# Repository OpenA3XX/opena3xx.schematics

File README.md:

# OpenA3XX Schematics & PCBs

## OpenA3XX Digital Hardare Controller Board (HCB)

## OpenA3XX MCDU with embedded HCB (Optional)
### Front View

### Back View

## OpenA3XX IO Terminal Block Boards

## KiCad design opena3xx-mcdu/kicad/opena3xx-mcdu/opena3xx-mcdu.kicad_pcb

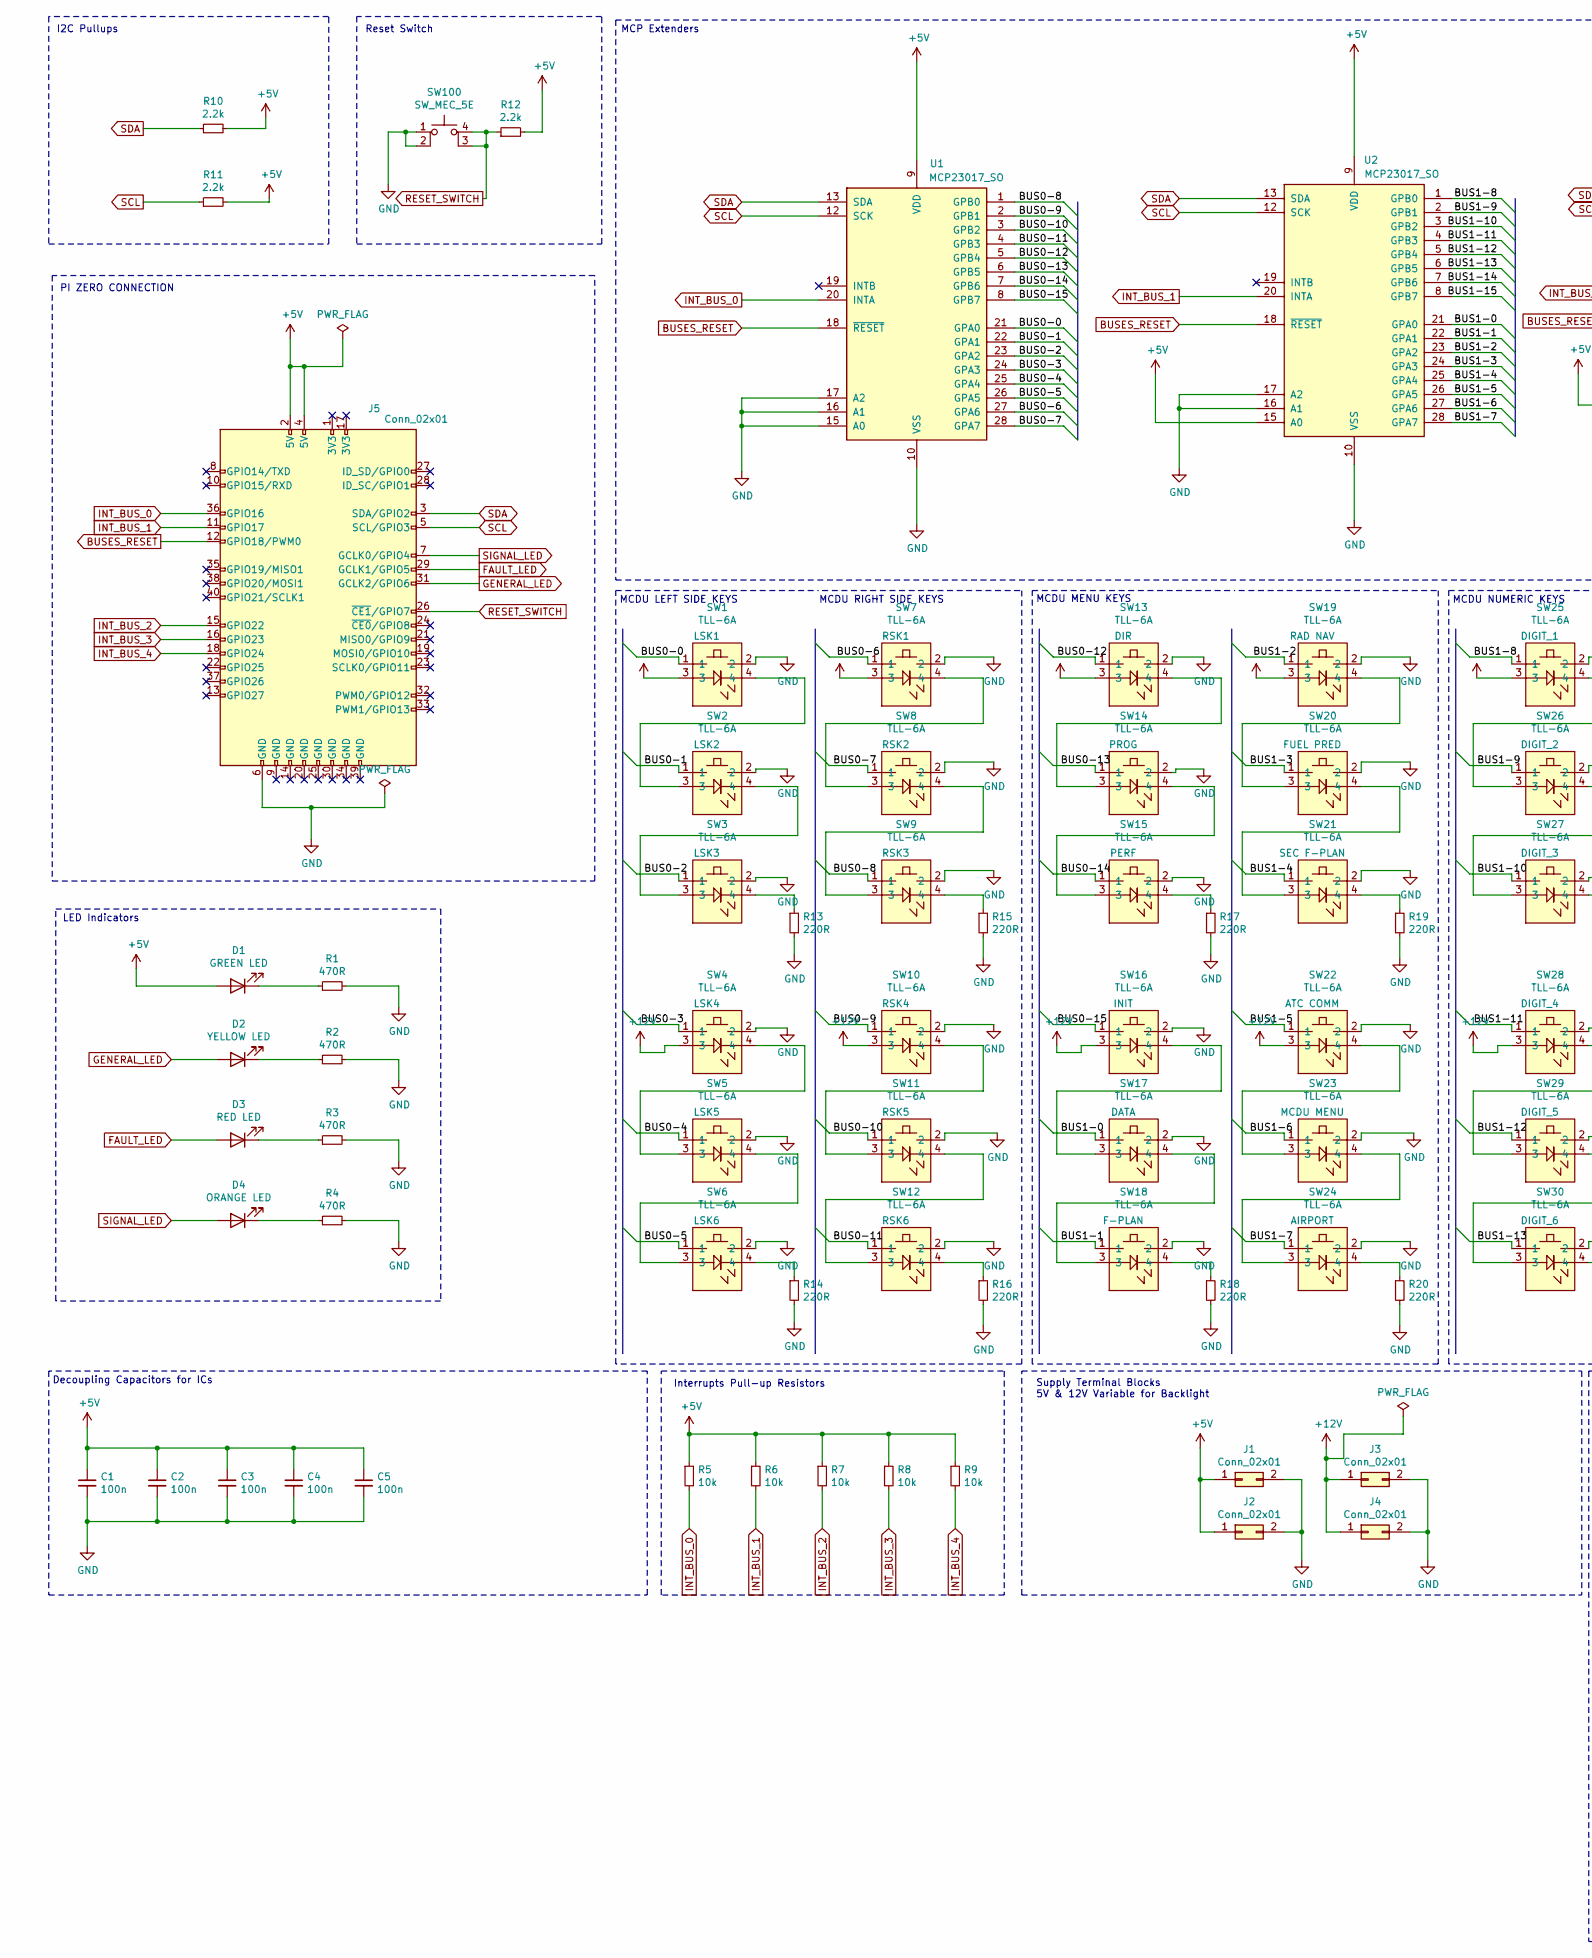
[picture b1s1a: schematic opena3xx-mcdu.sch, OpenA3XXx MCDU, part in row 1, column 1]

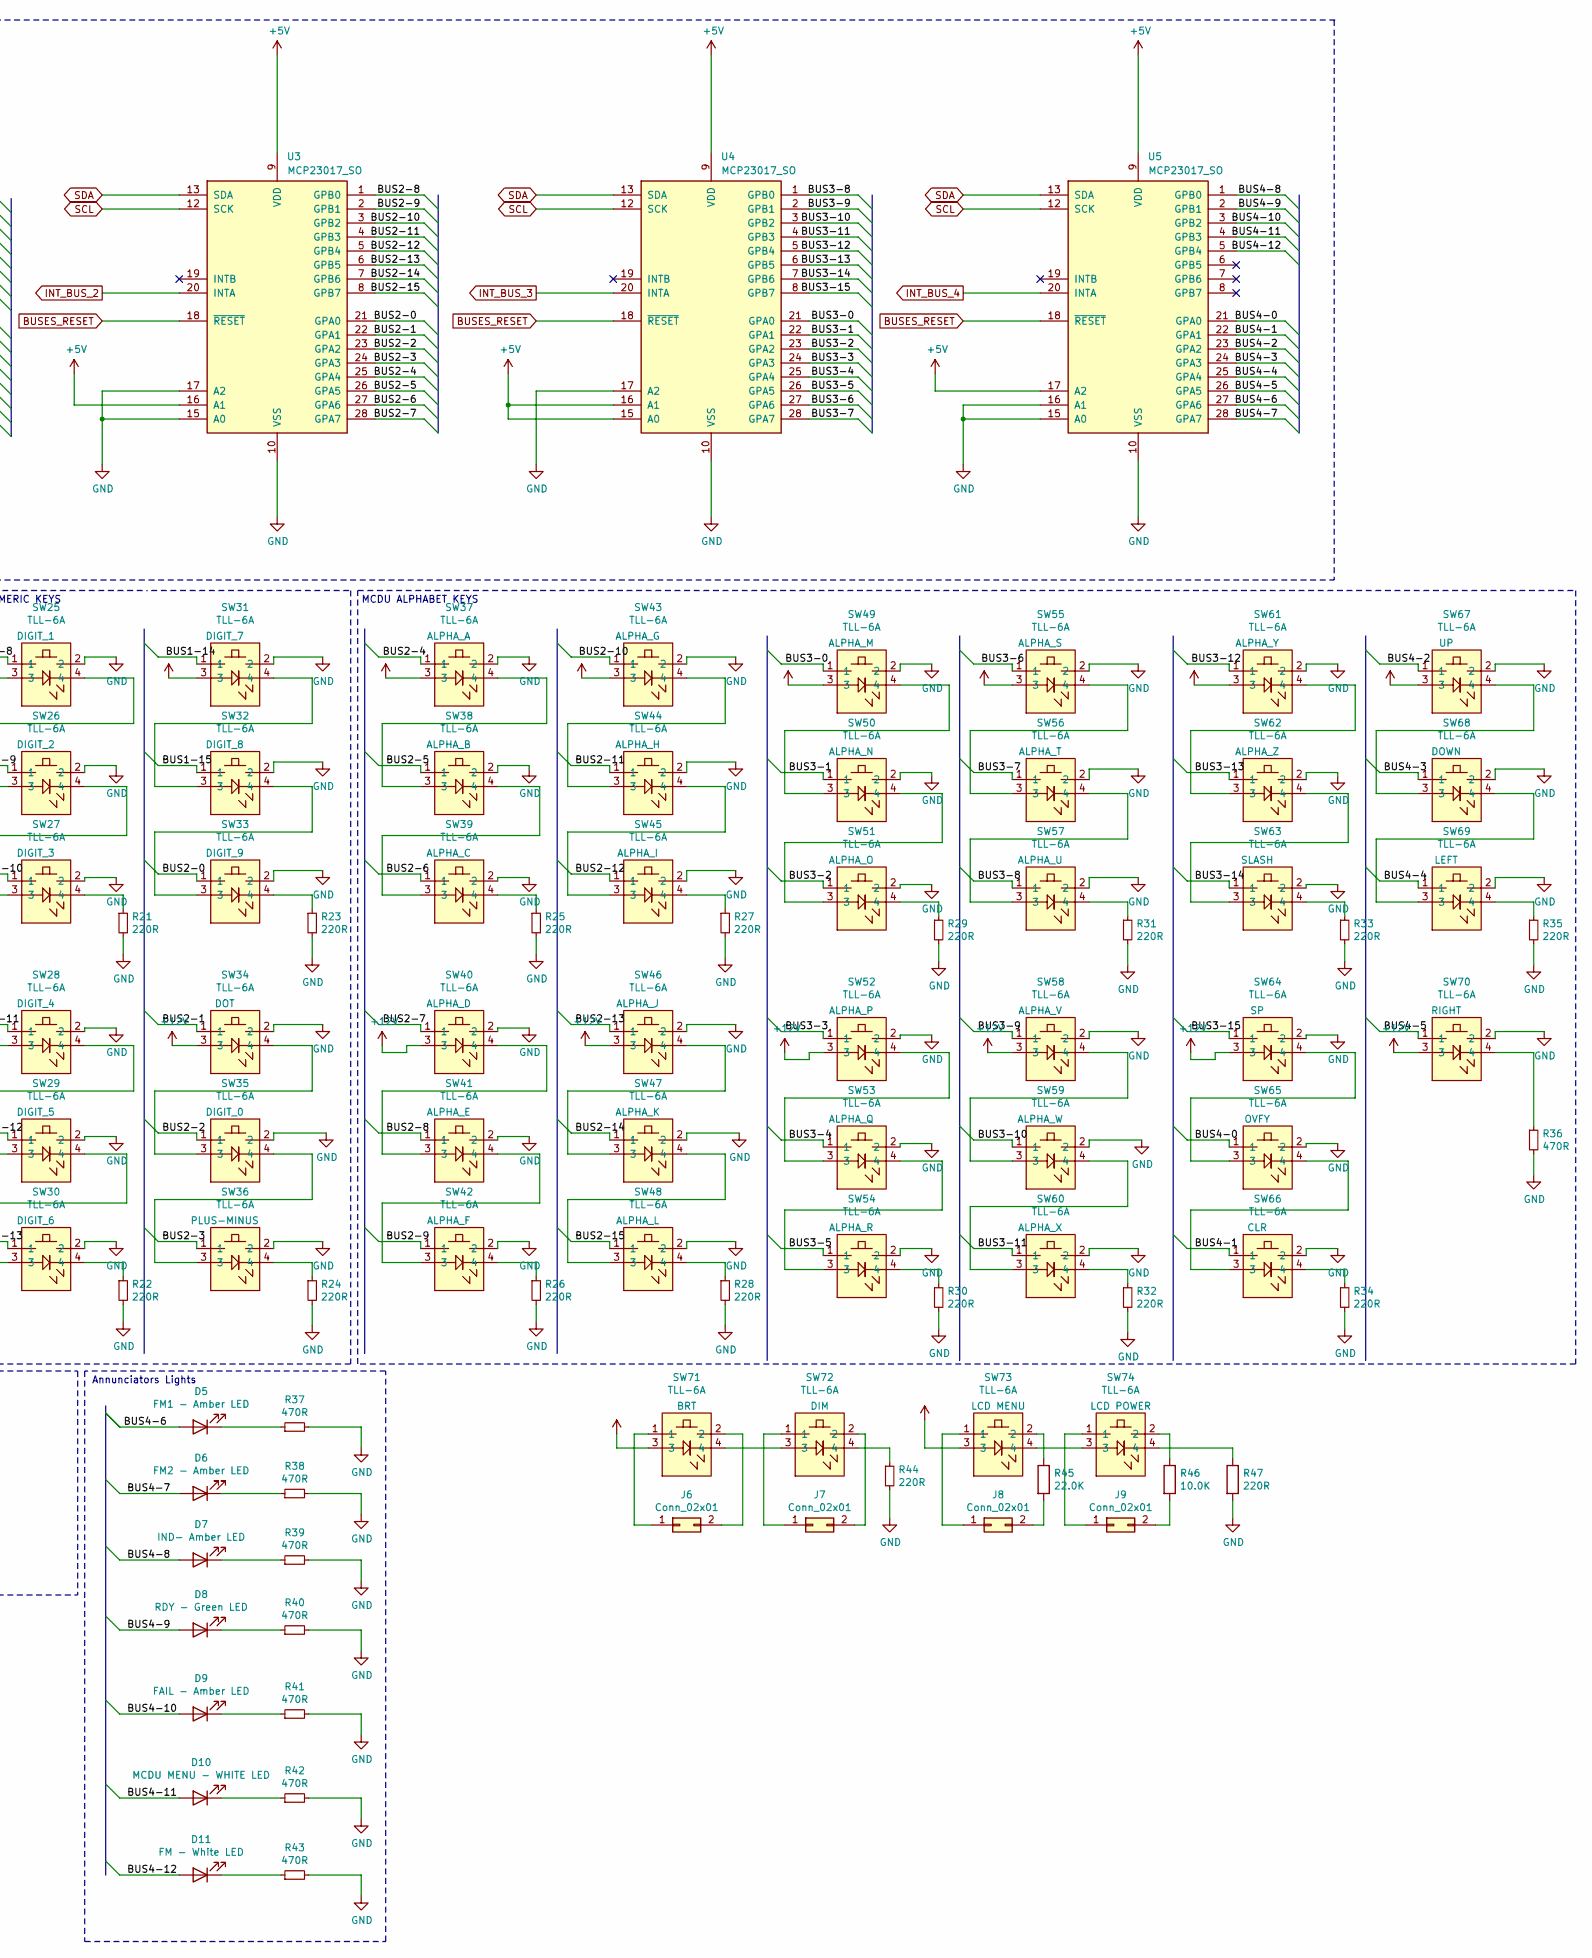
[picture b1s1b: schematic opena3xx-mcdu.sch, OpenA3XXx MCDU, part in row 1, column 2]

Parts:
C1, C2, C3, C4, C5: 100n; C_1206_3216Metric_Pad1.33x1.80mm_HandSolder
D1: GREEN LED; D_1206_3216Metric_Pad1.42x1.75mm_HandSolder
D2: YELLOW LED; D_1206_3216Metric_Pad1.42x1.75mm_HandSolder
D3: RED LED; D_1206_3216Metric_Pad1.42x1.75mm_HandSolder
D4: ORANGE LED; D_1206_3216Metric_Pad1.42x1.75mm_HandSolder
D5: FM1 - Amber LED; D_1206_3216Metric_Pad1.42x1.75mm_HandSolder
D6: FM2 - Amber LED; D_1206_3216Metric_Pad1.42x1.75mm_HandSolder
D7: IND- Amber LED; D_1206_3216Metric_Pad1.42x1.75mm_HandSolder
D8: RDY - Green LED; D_1206_3216Metric_Pad1.42x1.75mm_HandSolder
D9: FAIL - Amber LED; D_1206_3216Metric_Pad1.42x1.75mm_HandSolder
D10: MCDU MENU - WHITE LED; D_1206_3216Metric_Pad1.42x1.75mm_HandSolder
D11: FM - White LED; D_1206_3216Metric_Pad1.42x1.75mm_HandSolder
J1, J2, J3, J4, J6, J7, J8, J9: Conn_02x01; TerminalBlock_bornier-2_P5.08mm
J5: Conn_02x01; PinHeader_2x20_P2.54mm_Vertical
R1, R2, R3, R4, R37, R38, R39, R40, R41, R42, R43: 470R; R_1206_3216Metric_Pad1.30x1.75mm_HandSolder
R5, R6, R7, R8, R9: 10k; R_1206_3216Metric_Pad1.30x1.75mm_HandSolder
R10, R11, R12: 2.2k; R_1206_3216Metric_Pad1.30x1.75mm_HandSolder
R13, R14, R15, R16, R17, R18, R19, R20, R21, R22, R23, R24, R25, R26, R27, R28, R29, R30, R31, R32, R33, R34, R35, R44, R47: 220R; R_1210_3225Metric_Pad1.30x2.65mm_HandSolder
R36: 470R; R_1210_3225Metric_Pad1.30x2.65mm_HandSolder
R45: 22.0K; R_1210_3225Metric_Pad1.30x2.65mm_HandSolder
R46: 10.0K; R_1210_3225Metric_Pad1.30x2.65mm_HandSolder
SW1, SW2, SW3, SW4, SW5, SW6, SW7, SW8, SW9, SW10, SW11, SW12, SW13, SW14, SW15, SW16, SW17, SW18, SW19, SW20, SW21, SW22, SW23, SW24, SW25, SW26, SW27, SW28, SW29, SW30, SW31, SW32, SW33, SW34, SW35, SW36, SW37, SW38, SW39, SW40, SW41, SW42, SW43, SW44, SW45, SW46, SW47, SW48, SW49, SW50, SW51, SW52, SW53, SW54, SW55, SW56, SW57, SW58, SW59, SW60, SW61, SW62, SW63, SW64, SW65, SW66, SW67, SW68, SW69, SW70, SW71, SW72, SW73, SW74: TLL-6A; TACTILE_LED_TH
SW100: SW_MEC_5E; SW_TH_Tactile_Omron_B3F-10xx
U1, U2, U3, U4, U5: MCP23017_SO; SOIC-28W_7.5x17.9mm_P1.27mm

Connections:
+5V: C1.1, C2.1, C3.1, C4.1, C5.1, D1.2 (A), J1.1, J2.1, J5.2 (5V), J5.4 (5V), R5.1, R6.1, R7.1, R8.1, R9.1, R10.2, R11.2, R12.2, U1.9 (VDD), U2.9 (VDD), U2.15 (A0), U3.9 (VDD), U3.16 (A1), U4.9 (VDD), U4.15 (A0), U4.16 (A1), U5.9 (VDD), U5.17 (A2)
+12V: J3.1, J4.1, SW1.3, SW4.3, SW7.3, SW10.3, SW13.3, SW16.3, SW19.3, SW22.3, SW25.3, SW28.3, SW31.3, SW34.3, SW37.3, SW40.3, SW43.3, SW46.3, SW49.3, SW52.3, SW55.3, SW58.3, SW61.3, SW64.3, SW67.3, SW70.3, SW71.3, SW73.3
/BUS0-0: SW1.1, U1.21 (GPA0)
/BUS0-1: SW2.1, U1.22 (GPA1)
/BUS0-2: SW3.1, U1.23 (GPA2)
/BUS0-3: SW4.1, U1.24 (GPA3)
/BUS0-4: SW5.1, U1.25 (GPA4)
/BUS0-5: SW6.1, U1.26 (GPA5)
/BUS0-6: SW7.1, U1.27 (GPA6)
/BUS0-7: SW8.1, U1.28 (GPA7)
/BUS0-8: SW9.1, U1.1 (GPB0)
/BUS0-9: SW10.1, U1.2 (GPB1)
/BUS0-10: SW11.1, U1.3 (GPB2)
/BUS0-11: SW12.1, U1.4 (GPB3)
/BUS0-12: SW13.1, U1.5 (GPB4)
/BUS0-13: SW14.1, U1.6 (GPB5)
/BUS0-14: SW15.1, U1.7 (GPB6)
/BUS0-15: SW16.1, U1.8 (GPB7)
/BUS1-0: SW17.1, U2.21 (GPA0)
/BUS1-1: SW18.1, U2.22 (GPA1)
/BUS1-2: SW19.1, U2.23 (GPA2)
/BUS1-3: SW20.1, U2.24 (GPA3)
/BUS1-4: SW21.1, U2.25 (GPA4)
/BUS1-5: SW22.1, U2.26 (GPA5)
/BUS1-6: SW23.1, U2.27 (GPA6)
/BUS1-7: SW24.1, U2.28 (GPA7)
/BUS1-8: SW25.1, U2.1 (GPB0)
/BUS1-9: SW26.1, U2.2 (GPB1)
/BUS1-10: SW27.1, U2.3 (GPB2)
/BUS1-11: SW28.1, U2.4 (GPB3)
/BUS1-12: SW29.1, U2.5 (GPB4)
/BUS1-13: SW30.1, U2.6 (GPB5)
/BUS1-14: SW31.1, U2.7 (GPB6)
/BUS1-15: SW32.1, U2.8 (GPB7)
/BUS2-0: SW33.1, U3.21 (GPA0)
/BUS2-1: SW34.1, U3.22 (GPA1)
/BUS2-2: SW35.1, U3.23 (GPA2)
/BUS2-3: SW36.1, U3.24 (GPA3)
/BUS2-4: SW37.1, U3.25 (GPA4)
/BUS2-5: SW38.1, U3.26 (GPA5)
/BUS2-6: SW39.1, U3.27 (GPA6)
/BUS2-7: SW40.1, U3.28 (GPA7)
/BUS2-8: SW41.1, U3.1 (GPB0)
/BUS2-9: SW42.1, U3.2 (GPB1)
/BUS2-10: SW43.1, U3.3 (GPB2)
/BUS2-11: SW44.1, U3.4 (GPB3)
/BUS2-12: SW45.1, U3.5 (GPB4)
/BUS2-13: SW46.1, U3.6 (GPB5)
/BUS2-14: SW47.1, U3.7 (GPB6)
/BUS2-15: SW48.1, U3.8 (GPB7)
/BUS3-0: SW49.1, U4.21 (GPA0)
/BUS3-1: SW50.1, U4.22 (GPA1)
/BUS3-2: SW51.1, U4.23 (GPA2)
/BUS3-3: SW52.1, U4.24 (GPA3)
/BUS3-4: SW53.1, U4.25 (GPA4)
/BUS3-5: SW54.1, U4.26 (GPA5)
/BUS3-6: SW55.1, U4.27 (GPA6)
/BUS3-7: SW56.1, U4.28 (GPA7)
/BUS3-8: SW57.1, U4.1 (GPB0)
/BUS3-9: SW58.1, U4.2 (GPB1)
/BUS3-10: SW59.1, U4.3 (GPB2)
/BUS3-11: SW60.1, U4.4 (GPB3)
/BUS3-12: SW61.1, U4.5 (GPB4)
/BUS3-13: SW62.1, U4.6 (GPB5)
/BUS3-14: SW63.1, U4.7 (GPB6)
/BUS3-15: SW64.1, U4.8 (GPB7)
/BUS4-0: SW65.1, U5.21 (GPA0)
/BUS4-1: SW66.1, U5.22 (GPA1)
/BUS4-2: SW67.1, U5.23 (GPA2)
/BUS4-3: SW68.1, U5.24 (GPA3)
/BUS4-4: SW69.1, U5.25 (GPA4)
/BUS4-5: SW70.1, U5.26 (GPA5)
/BUS4-6: D5.2 (A), U5.27 (GPA6)
/BUS4-7: D6.2 (A), U5.28 (GPA7)
/BUS4-8: D7.2 (A), U5.1 (GPB0)
/BUS4-9: D8.2 (A), U5.2 (GPB1)
/BUS4-10: D9.2 (A), U5.3 (GPB2)
/BUS4-11: D10.2 (A), U5.4 (GPB3)
/BUS4-12: D11.2 (A), U5.5 (GPB4)
BUSES_RESET: J5.12 (GPIO18/PWM0), U1.18 (~RESET~), U2.18 (~RESET~), U3.18 (~RESET~), U4.18 (~RESET~), U5.18 (~RESET~)
FAULT_LED: D3.2 (A), J5.29 (GCLK1/GPIO5)
GENERAL_LED: D2.2 (A), J5.31 (GCLK2/GPIO6)
GND: C1.2, C2.2, C3.2, C4.2, C5.2, J1.2, J2.2, J3.2, J4.2, J5.6 (GND), R1.2, R2.2, R3.2, R4.2, R13.2, R14.2, R15.2, R16.2, R17.2, R18.2, R19.2, R20.2, R21.2, R22.2, R23.2, R24.2, R25.2, R26.2, R27.2, R28.2, R29.2, R30.2, R31.2, R32.2, R33.2, R34.2, R35.2, R36.2, R37.2, R38.2, R39.2, R40.2, R41.2, R42.2, R43.2, R44.2, R47.2, SW1.2, SW2.2, SW3.2, SW4.2, SW5.2, SW6.2, SW7.2, SW8.2, SW9.2, SW10.2, SW11.2, SW12.2, SW13.2, SW14.2, SW15.2, SW16.2, SW17.2, SW18.2, SW19.2, SW20.2, SW21.2, SW22.2, SW23.2, SW24.2, SW25.2, SW26.2, SW27.2, SW28.2, SW29.2, SW30.2, SW31.2, SW32.2, SW33.2, SW34.2, SW35.2, SW36.2, SW37.2, SW38.2, SW39.2, SW40.2, SW41.2, SW42.2, SW43.2, SW44.2, SW45.2, SW46.2, SW47.2, SW48.2, SW49.2, SW50.2, SW51.2, SW52.2, SW53.2, SW54.2, SW55.2, SW56.2, SW57.2, SW58.2, SW59.2, SW60.2, SW61.2, SW62.2, SW63.2, SW64.2, SW65.2, SW66.2, SW67.2, SW68.2, SW69.2, SW70.2, SW100.1, SW100.2, U1.10 (VSS), U1.15 (A0), U1.16 (A1), U1.17 (A2), U2.10 (VSS), U2.16 (A1), U2.17 (A2), U3.10 (VSS), U3.15 (A0), U3.17 (A2), U4.10 (VSS), U4.17 (A2), U5.10 (VSS), U5.15 (A0), U5.16 (A1)
INT_BUS_0: J5.36 (GPIO16), R5.2, U1.20 (INTA)
INT_BUS_1: J5.11 (GPIO17), R6.2, U2.20 (INTA)
INT_BUS_2: J5.15 (GPIO22), R7.2, U3.20 (INTA)
INT_BUS_3: J5.16 (GPIO23), R8.2, U4.20 (INTA)
INT_BUS_4: J5.18 (GPIO24), R9.2, U5.20 (INTA)
unnamed: D1.1 (K), R1.1
unnamed: D2.1 (K), R2.1
unnamed: D3.1 (K), R3.1
unnamed: D4.1 (K), R4.1
unnamed: D5.1 (K), R37.1
unnamed: D6.1 (K), R38.1
unnamed: D7.1 (K), R39.1
unnamed: D8.1 (K), R40.1
unnamed: D9.1 (K), R41.1
unnamed: D10.1 (K), R42.1
unnamed: D11.1 (K), R43.1
unnamed: J6.1, SW71.1
unnamed: J6.2, SW71.2
unnamed: J7.1, SW72.1
unnamed: J7.2, SW72.2
unnamed: J8.1, SW73.1
unnamed: J8.2, R45.2
unnamed: J9.1, SW74.1
unnamed: J9.2, R46.2
unnamed: R13.1, SW3.4
unnamed: R14.1, SW6.4
unnamed: R15.1, SW9.4
unnamed: R16.1, SW12.4
unnamed: R17.1, SW15.4
unnamed: R18.1, SW18.4
unnamed: R19.1, SW21.4
unnamed: R20.1, SW24.4
unnamed: R21.1, SW27.4
unnamed: R22.1, SW30.4
unnamed: R23.1, SW33.4
unnamed: R24.1, SW36.4
unnamed: R25.1, SW39.4
unnamed: R26.1, SW42.4
unnamed: R27.1, SW45.4
unnamed: R28.1, SW48.4
unnamed: R29.1, SW51.4
unnamed: R30.1, SW54.4
unnamed: R31.1, SW57.4
unnamed: R32.1, SW60.4
unnamed: R33.1, SW63.4
unnamed: R34.1, SW66.4
unnamed: R35.1, SW69.4
unnamed: R36.1, SW70.4
unnamed: R44.1, SW72.4
unnamed: R45.1, SW73.2
unnamed: R46.1, SW74.2
unnamed: R47.1, SW74.4
unnamed: SW1.4, SW2.3
unnamed: SW2.4, SW3.3
unnamed: SW4.4, SW5.3
unnamed: SW5.4, SW6.3
unnamed: SW7.4, SW8.3
unnamed: SW8.4, SW9.3
unnamed: SW10.4, SW11.3
unnamed: SW11.4, SW12.3
unnamed: SW13.4, SW14.3
unnamed: SW14.4, SW15.3
unnamed: SW16.4, SW17.3
unnamed: SW17.4, SW18.3
unnamed: SW19.4, SW20.3
unnamed: SW20.4, SW21.3
unnamed: SW22.4, SW23.3
unnamed: SW23.4, SW24.3
unnamed: SW25.4, SW26.3
unnamed: SW26.4, SW27.3
unnamed: SW28.4, SW29.3
unnamed: SW29.4, SW30.3
unnamed: SW31.4, SW32.3
unnamed: SW32.4, SW33.3
unnamed: SW34.4, SW35.3
unnamed: SW35.4, SW36.3
unnamed: SW37.4, SW38.3
unnamed: SW38.4, SW39.3
unnamed: SW40.4, SW41.3
unnamed: SW41.4, SW42.3
unnamed: SW43.4, SW44.3
unnamed: SW44.4, SW45.3
unnamed: SW46.4, SW47.3
unnamed: SW47.4, SW48.3
unnamed: SW49.4, SW50.3
unnamed: SW50.4, SW51.3
unnamed: SW52.4, SW53.3
unnamed: SW53.4, SW54.3
unnamed: SW55.4, SW56.3
unnamed: SW56.4, SW57.3
unnamed: SW58.4, SW59.3
unnamed: SW59.4, SW60.3
unnamed: SW61.4, SW62.3
unnamed: SW62.4, SW63.3
unnamed: SW64.4, SW65.3
unnamed: SW65.4, SW66.3
unnamed: SW67.4, SW68.3
unnamed: SW68.4, SW69.3
unnamed: SW71.4, SW72.3
unnamed: SW73.4, SW74.3
RESET_SWITCH: J5.26 (~CE1~/GPIO7), R12.1, SW100.3 (K), SW100.4 (A)
SCL: J5.5 (SCL/GPIO3), R11.1, U1.12 (SCK), U2.12 (SCK), U3.12 (SCK), U4.12 (SCK), U5.12 (SCK)
SDA: J5.3 (SDA/GPIO2), R10.1, U1.13 (SDA), U2.13 (SDA), U3.13 (SDA), U4.13 (SDA), U5.13 (SDA)
SIGNAL_LED: D4.2 (A), J5.7 (GCLK0/GPIO4)

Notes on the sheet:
I2C Pullups
LED Indicators
PI ZERO CONNECTION
MCP Extenders
Decoupling Capacitors for ICs
Interrupts Pull-up Resistors
Supply Terminal Blocks 5V & 12V Variable for Backlight
Reset Switch
MCDU LEFT SIDE KEYS
MCDU RIGHT SIDE KEYS
MCDU MENU KEYS
MCDU NUMERIC KEYS
MCDU ALPHABET KEYS
Annunciators Lights

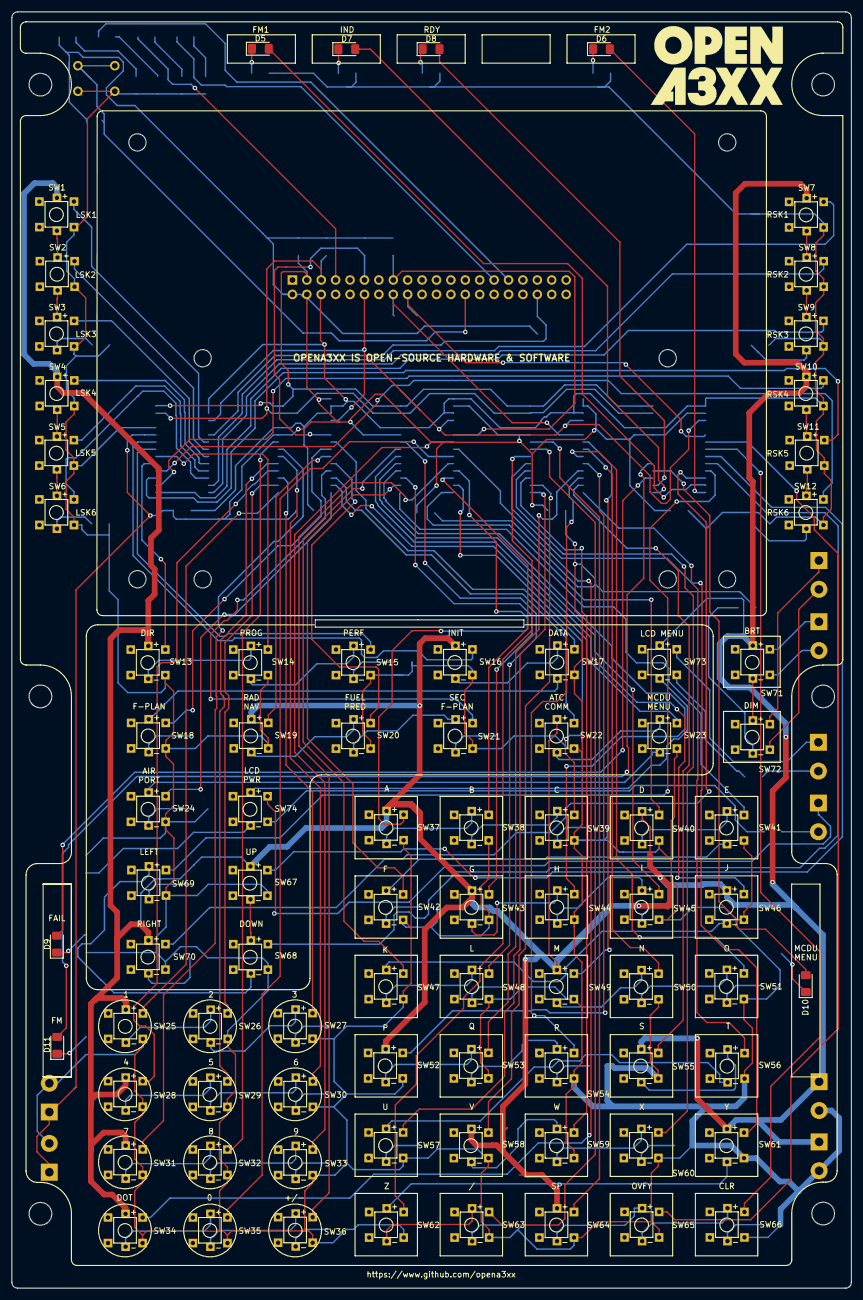
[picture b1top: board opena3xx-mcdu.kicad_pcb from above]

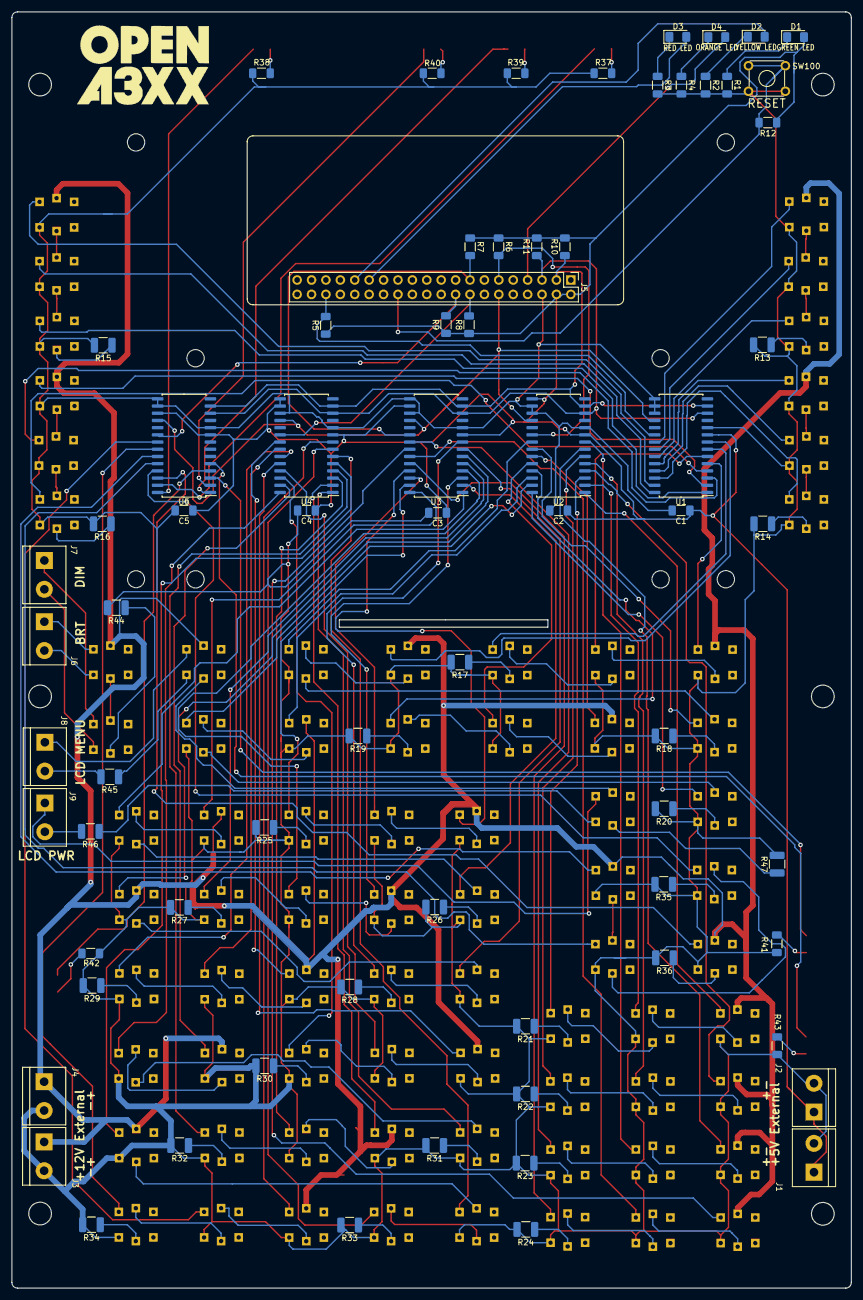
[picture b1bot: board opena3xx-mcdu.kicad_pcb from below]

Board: 2 copper layers, 148.0 x 225.0 mm, 152 parts (71 on the bottom side), 187 nets.

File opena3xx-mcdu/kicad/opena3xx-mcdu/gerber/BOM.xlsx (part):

Comment | Designator | Footprint | LCSC Part #（optional）
Terminal Block | J1 | Conn_02x01_TerminalBlock | C8404
Terminal Block | J2 | Conn_02x01_TerminalBlock | C8404
Terminal Block | J3 | Conn_02x01_TerminalBlock | C8404
Terminal Block | J4 | Conn_02x01_TerminalBlock | C8404
Terminal Block | J6 | Conn_02x01_TerminalBlock | C8404
Terminal Block | J7 | Conn_02x01_TerminalBlock | C8404
Terminal Block | J8 | Conn_02x01_TerminalBlock | C8404
Terminal Block | J9 | Conn_02x01_TerminalBlock | C8404
Tactile Switch with LED | SW1 | TLL-6A_TACTILE_LED_TH | C354965
Tactile Switch with LED | SW2 | TLL-6A_TACTILE_LED_TH | C354965
Tactile Switch with LED | SW3 | TLL-6A_TACTILE_LED_TH | C354965
Tactile Switch with LED | SW4 | TLL-6A_TACTILE_LED_TH | C354965
Tactile Switch with LED | SW5 | TLL-6A_TACTILE_LED_TH | C354965
Tactile Switch with LED | SW6 | TLL-6A_TACTILE_LED_TH | C354965
Tactile Switch with LED | SW7 | TLL-6A_TACTILE_LED_TH | C354965
Tactile Switch with LED | SW8 | TLL-6A_TACTILE_LED_TH | C354965
Tactile Switch with LED | SW9 | TLL-6A_TACTILE_LED_TH | C354965
Tactile Switch with LED | SW10 | TLL-6A_TACTILE_LED_TH | C354965
Tactile Switch with LED | SW11 | TLL-6A_TACTILE_LED_TH | C354965
Tactile Switch with LED | SW12 | TLL-6A_TACTILE_LED_TH | C354965
Tactile Switch with LED | SW13 | TLL-6A_TACTILE_LED_TH | C354965
Tactile Switch with LED | SW14 | TLL-6A_TACTILE_LED_TH | C354965
Tactile Switch with LED | SW15 | TLL-6A_TACTILE_LED_TH | C354965
Tactile Switch with LED | SW16 | TLL-6A_TACTILE_LED_TH | C354965
Tactile Switch with LED | SW17 | TLL-6A_TACTILE_LED_TH | C354965
Tactile Switch with LED | SW18 | TLL-6A_TACTILE_LED_TH | C354965
Tactile Switch with LED | SW19 | TLL-6A_TACTILE_LED_TH | C354965
Tactile Switch with LED | SW20 | TLL-6A_TACTILE_LED_TH | C354965
Tactile Switch with LED | SW21 | TLL-6A_TACTILE_LED_TH | C354965
Tactile Switch with LED | SW22 | TLL-6A_TACTILE_LED_TH | C354965
Tactile Switch with LED | SW23 | TLL-6A_TACTILE_LED_TH | C354965
Tactile Switch with LED | SW24 | TLL-6A_TACTILE_LED_TH | C354965
Tactile Switch with LED | SW25 | TLL-6A_TACTILE_LED_TH | C354965
Tactile Switch with LED | SW26 | TLL-6A_TACTILE_LED_TH | C354965
Tactile Switch with LED | SW27 | TLL-6A_TACTILE_LED_TH | C354965
Tactile Switch with LED | SW28 | TLL-6A_TACTILE_LED_TH | C354965
Tactile Switch with LED | SW29 | TLL-6A_TACTILE_LED_TH | C354965
Tactile Switch with LED | SW30 | TLL-6A_TACTILE_LED_TH | C354965
Tactile Switch with LED | SW31 | TLL-6A_TACTILE_LED_TH | C354965
Tactile Switch with LED | SW32 | TLL-6A_TACTILE_LED_TH | C354965
Tactile Switch with LED | SW33 | TLL-6A_TACTILE_LED_TH | C354965
Tactile Switch with LED | SW34 | TLL-6A_TACTILE_LED_TH | C354965
Tactile Switch with LED | SW35 | TLL-6A_TACTILE_LED_TH | C354965
Tactile Switch with LED | SW36 | TLL-6A_TACTILE_LED_TH | C354965
Tactile Switch with LED | SW37 | TLL-6A_TACTILE_LED_TH | C354965
Tactile Switch with LED | SW38 | TLL-6A_TACTILE_LED_TH | C354965
Tactile Switch with LED | SW39 | TLL-6A_TACTILE_LED_TH | C354965
Tactile Switch with LED | SW40 | TLL-6A_TACTILE_LED_TH | C354965
Tactile Switch with LED | SW41 | TLL-6A_TACTILE_LED_TH | C354965
Tactile Switch with LED | SW42 | TLL-6A_TACTILE_LED_TH | C354965
Tactile Switch with LED | SW43 | TLL-6A_TACTILE_LED_TH | C354965
Tactile Switch with LED | SW44 | TLL-6A_TACTILE_LED_TH | C354965
Tactile Switch with LED | SW45 | TLL-6A_TACTILE_LED_TH | C354965
Tactile Switch with LED | SW46 | TLL-6A_TACTILE_LED_TH | C354965
Tactile Switch with LED | SW47 | TLL-6A_TACTILE_LED_TH | C354965
Tactile Switch with LED | SW48 | TLL-6A_TACTILE_LED_TH | C354965
Tactile Switch with LED | SW49 | TLL-6A_TACTILE_LED_TH | C354965
Tactile Switch with LED | SW50 | TLL-6A_TACTILE_LED_TH | C354965
Tactile Switch with LED | SW51 | TLL-6A_TACTILE_LED_TH | C354965
Tactile Switch with LED | SW52 | TLL-6A_TACTILE_LED_TH | C354965
Tactile Switch with LED | SW53 | TLL-6A_TACTILE_LED_TH | C354965
Tactile Switch with LED | SW54 | TLL-6A_TACTILE_LED_TH | C354965
Tactile Switch with LED | SW55 | TLL-6A_TACTILE_LED_TH | C354965
Tactile Switch with LED | SW56 | TLL-6A_TACTILE_LED_TH | C354965
Tactile Switch with LED | SW57 | TLL-6A_TACTILE_LED_TH | C354965
Tactile Switch with LED | SW58 | TLL-6A_TACTILE_LED_TH | C354965
Tactile Switch with LED | SW59 | TLL-6A_TACTILE_LED_TH | C354965
Tactile Switch with LED | SW60 | TLL-6A_TACTILE_LED_TH | C354965
Tactile Switch with LED | SW61 | TLL-6A_TACTILE_LED_TH | C354965
Tactile Switch with LED | SW62 | TLL-6A_TACTILE_LED_TH | C354965
Tactile Switch with LED | SW63 | TLL-6A_TACTILE_LED_TH | C354965
Tactile Switch with LED | SW64 | TLL-6A_TACTILE_LED_TH | C354965
Tactile Switch with LED | SW65 | TLL-6A_TACTILE_LED_TH | C354965
Tactile Switch with LED | SW66 | TLL-6A_TACTILE_LED_TH | C354965
Tactile Switch with LED | SW67 | TLL-6A_TACTILE_LED_TH | C354965
Tactile Switch with LED | SW68 | TLL-6A_TACTILE_LED_TH | C354965
Tactile Switch with LED | SW69 | TLL-6A_TACTILE_LED_TH | C354965
Tactile Switch with LED | SW70 | TLL-6A_TACTILE_LED_TH | C354965
Tactile Switch with LED | SW71 | TLL-6A_TACTILE_LED_TH | C354965
Tactile Switch with LED | SW72 | TLL-6A_TACTILE_LED_TH | C354965
Tactile Switch with LED | SW73 | TLL-6A_TACTILE_LED_TH | C354965
Tactile Switch with LED | SW74 | TLL-6A_TACTILE_LED_TH | C354965
220R | R13 | R_1210_3225Metric | C17957
220R | R14 | R_1210_3225Metric | C17957
220R | R15 | R_1210_3225Metric | C17957
220R | R16 | R_1210_3225Metric | C17957
220R | R17 | R_1210_3225Metric | C17957
220R | R18 | R_1210_3225Metric | C17957
220R | R19 | R_1210_3225Metric | C17957
220R | R20 | R_1210_3225Metric | C17957
220R | R21 | R_1210_3225Metric | C17957
220R | R22 | R_1210_3225Metric | C17957
220R | R23 | R_1210_3225Metric | C17957
220R | R24 | R_1210_3225Metric | C17957
220R | R25 | R_1210_3225Metric | C17957
220R | R26 | R_1210_3225Metric | C17957
220R | R27 | R_1210_3225Metric | C17957
220R | R28 | R_1210_3225Metric | C17957
220R | R29 | R_1210_3225Metric | C17957
220R | R30 | R_1210_3225Metric | C17957
220R | R31 | R_1210_3225Metric | C17957
220R | R32 | R_1210_3225Metric | C17957
220R | R33 | R_1210_3225Metric | C17957
220R | R34 | R_1210_3225Metric | C17957
220R | R35 | R_1210_3225Metric | C17957
220R | R44 | R_1210_3225Metric | C17957
MCP23017_SO | U1 | SOIC-28W | C47023
MCP23017_SO | U2 | SOIC-28W | C47023
MCP23017_SO | U3 | SOIC-28W | C47023
MCP23017_SO | U4 | SOIC-28W | C47023
MCP23017_SO | U5 | SOIC-28W | C47023
Tactile Switch MEC_5E | SW100 | SW_TH_Tactile_Omron_B3F-10xx | C111609
470R | R43 | R_1206_3216Metric | C4502
470R | R42 | R_1206_3216Metric | C4502
470R | R41 | R_1206_3216Metric | C4502
470R | R40 | R_1206_3216Metric | C4502
470R | R39 | R_1206_3216Metric | C4502
470R | R38 | R_1206_3216Metric | C4502
470R | R37 | R_1206_3216Metric | C4502
470R | R4 | R_1206_3216Metric | C4502
470R | R3 | R_1206_3216Metric | C4502
470R | R2 | R_1206_3216Metric | C4502
470R | R36 | R_1206_3216Metric | C4502
470R | R1 | R_1206_3216Metric | C4502
2.2K | R12 | R_1206_3216Metric | C17948
2.2K | R11 | R_1206_3216Metric | C17948
2.2K | R10 | R_1206_3216Metric | C17948
10K | R9 | R_1206_3216Metric | C17902
10K | R8 | R_1206_3216Metric | C17902
10K | R7 | R_1206_3216Metric | C17902
10K | R6 | R_1206_3216Metric | C17902
10K | R5 | R_1206_3216Metric | C17902
2x20 2.54mm Vertical | J5 | Conn_02x20_MountingPin | C124383
White LED | D11 | D_1206_3216Metric | C130718
White LED | D10 | D_1206_3216Metric | C130718
Amber LED | D9 | D_1206_3216Metric | C93094
Green LED | D8 | D_1206_3216Metric | C434439
Amber LED | D7 | D_1206_3216Metric | C93094
Amber LED | D6 | D_1206_3216Metric | C93094
Amber LED | D5 | D_1206_3216Metric | C93094
Orange LED | D4 | D_1206_3216Metric | C93094
Red LED | D3 | D_1206_3216Metric | C192674
Yellow LED | D2 | D_1206_3216Metric | C93094
Green LED | D1 | D_1206_3216Metric | C434439
100n Capacitor | C1 | C_1206_3216Metric | C24497
100n Capacitor | C2 | C_1206_3216Metric | C24497
100n Capacitor | C3 | C_1206_3216Metric | C24497
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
